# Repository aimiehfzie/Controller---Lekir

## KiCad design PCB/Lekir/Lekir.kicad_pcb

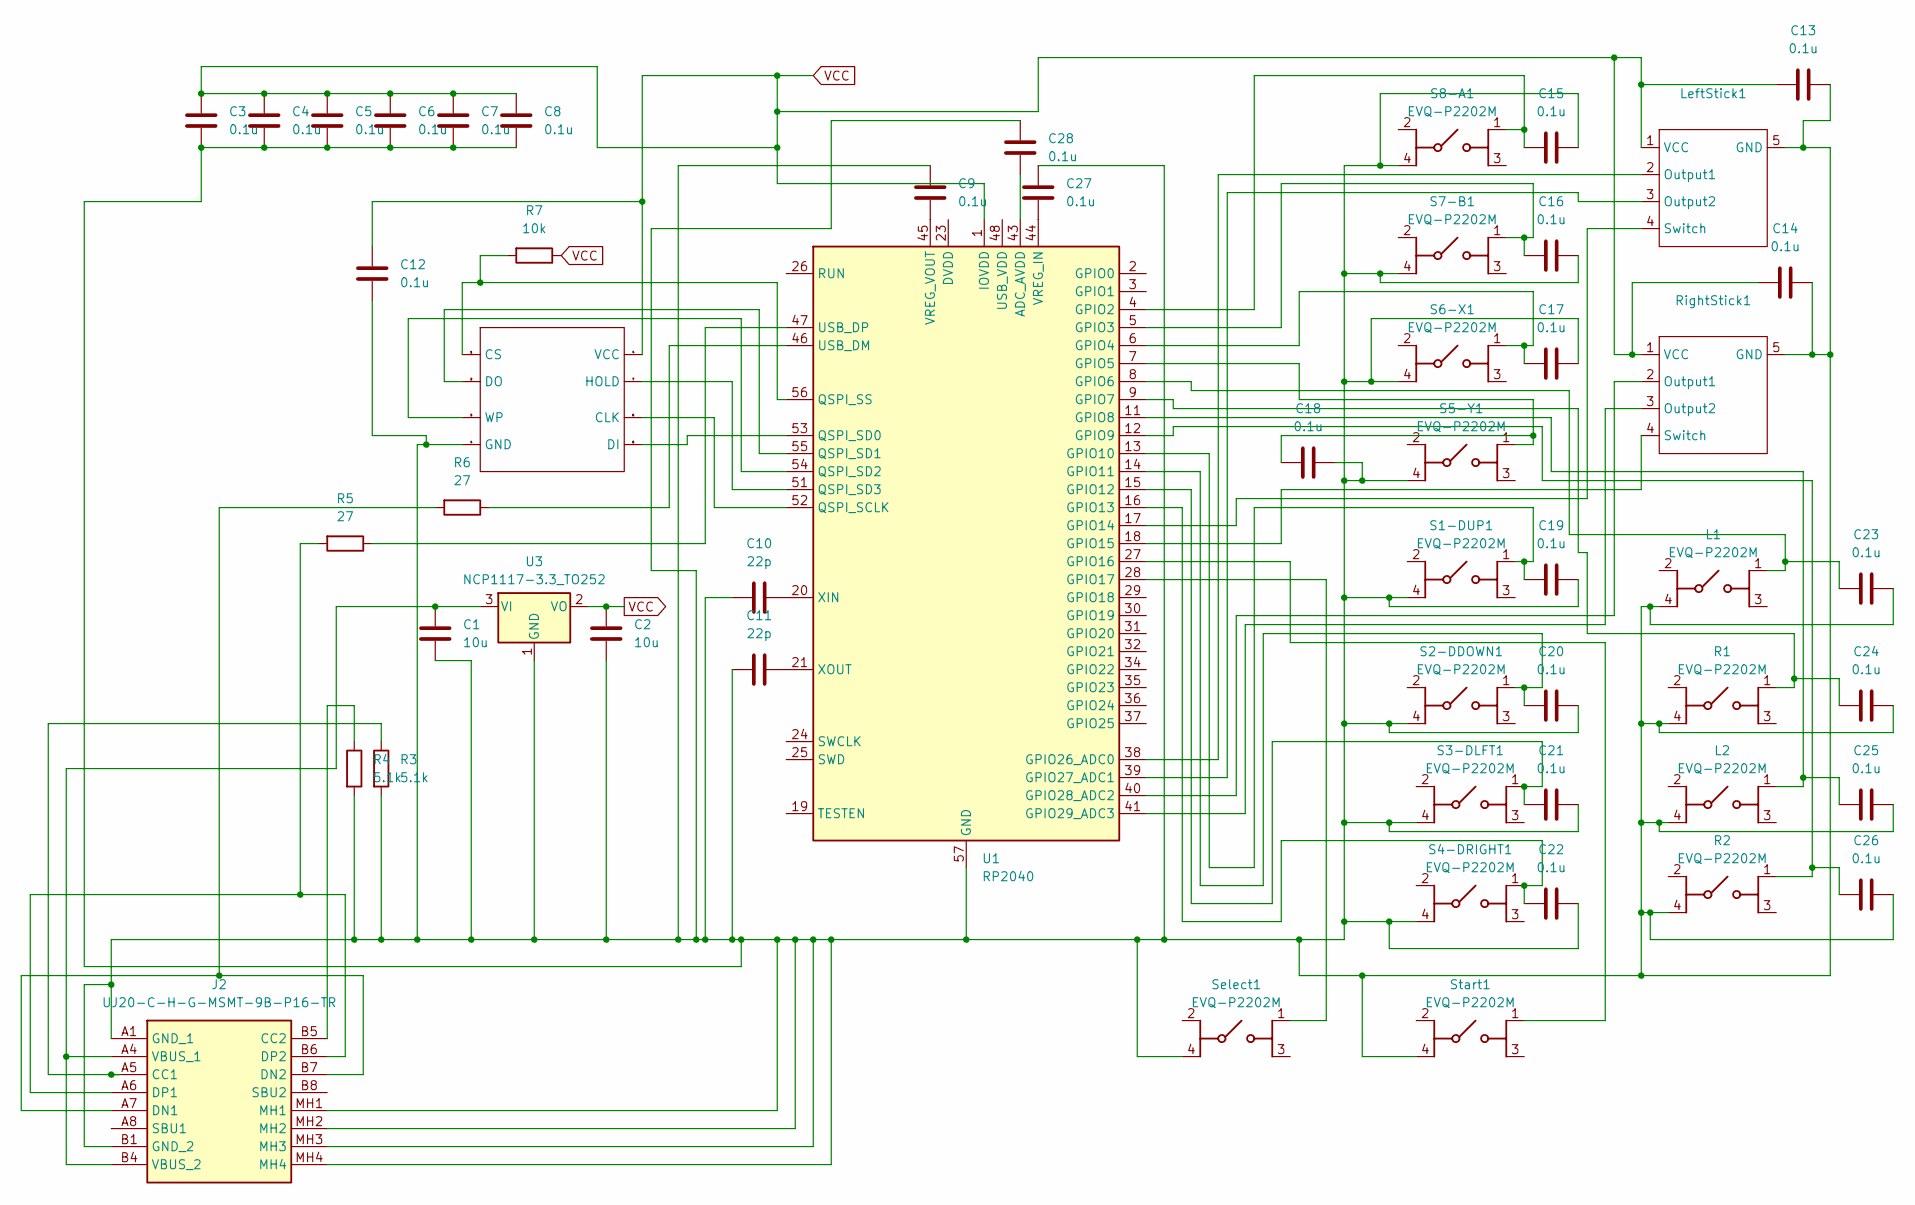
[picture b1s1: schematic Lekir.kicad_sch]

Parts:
C1, C2: 10u; CAPC1005X70N
C3, C4, C5, C6, C7, C8, C9, C12, C13, C14, C15, C16, C17, C18, C19, C20, C21, C22, C23, C24, C25, C26, C27, C28: 0.1u; CAPC1005X55N
C10, C11: 22p; CAPC1608X90N
J2: UJ20-C-H-G-MSMT-9B-P16-TR; UJ20CHGMSMT9BP16TR; Manufacturer_Part_Number UJ20-C-H-G-MSMT-9B-P16-TR
L1, L2: EVQ-P2202M; EVQP2202M; Mouser Part Number 667-EVQ-P2202M
LeftStick1: JH16-KSilver
R1, R2: EVQ-P2202M; EVQP2202M; Mouser Part Number 667-EVQ-P2202M
R3, R4: 5.1k; RESC3216X70N
R5, R6: 27; ERA2AED122X
R7: 10k; ERA2AED122X
RightStick1: JH16-KSilver
S1-DUP1, S2-DDOWN1, S3-DLFT1, S4-DRIGHT1, S5-Y1, S6-X1, S7-B1, S8-A1: EVQ-P2202M; EVQP2202M; Mouser Part Number 667-EVQ-P2202M
Select1: EVQ-P2202M; EVQP2202M; Mouser Part Number 667-EVQ-P2202M
Start1: EVQ-P2202M; EVQP2202M; Mouser Part Number 667-EVQ-P2202M
U1: RP2040; QFN-56-1EP_7x7mm_P0.4mm_EP3.2x3.2mm
U2: Flash
U3: NCP1117-3.3_TO252; TO-252-2

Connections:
unnamed: J2.A5 (CC1), R3.1
unnamed: J2.B5 (CC2), R4.1
unnamed: J2.A7 (DN1), J2.B7 (DN2), R6.2
unnamed: J2.A6 (DP1), J2.B6 (DP2), R5.2
unnamed: C1.1, J2.A4 (VBUS_1), J2.B4 (VBUS_2), U3.3 (VI)
unnamed: C23.2, L1.1 (NO_1), U1.8 (GPIO6)
unnamed: C25.2, L2.1 (NO_1), U1.11 (GPIO8)
unnamed: LeftStick1.2 (Output1), U1.38 (GPIO26_ADC0)
unnamed: LeftStick1.3 (Output2), U1.39 (GPIO27_ADC1)
unnamed: LeftStick1.4 (Switch), U1.17 (GPIO14)
unnamed: C24.2, R1.1 (NO_1), U1.9 (GPIO7)
unnamed: C26.2, R2.1 (NO_1), U1.12 (GPIO9)
unnamed: RightStick1.2 (Output1), U1.40 (GPIO28_ADC2)
unnamed: RightStick1.3 (Output2), U1.41 (GPIO29_ADC3)
unnamed: RightStick1.4 (Switch), U1.18 (GPIO15)
unnamed: C19.2, S1-DUP1.1 (NO_1), U1.13 (GPIO10)
unnamed: C20.2, S2-DDOWN1.1 (NO_1), U1.14 (GPIO11)
unnamed: C21.2, S3-DLFT1.1 (NO_1), U1.15 (GPIO12)
unnamed: C22.2, S4-DRIGHT1.1 (NO_1), U1.16 (GPIO13)
unnamed: C18.2, S5-Y1.1 (NO_1), U1.7 (GPIO5)
unnamed: C17.2, S6-X1.1 (NO_1), U1.6 (GPIO4)
unnamed: C16.2, S7-B1.1 (NO_1), U1.5 (GPIO3)
unnamed: C15.2, S8-A1.1 (NO_1), U1.4 (GPIO2)
unnamed: Select1.1 (NO_1), U1.28 (GPIO17)
unnamed: Start1.1 (NO_1), U1.27 (GPIO16)
unnamed: C28.2, U1.43 (ADC_AVDD)
unnamed: U1.23 (DVDD), U1.50 (DVDD)
unnamed: U1.52 (QSPI_SCLK), U2.6 (CLK)
unnamed: U1.53 (QSPI_SD0), U2.5 (DI)
unnamed: U1.55 (QSPI_SD1), U2.2 (DO)
unnamed: U1.54 (QSPI_SD2), U2.3 (WP)
unnamed: U1.51 (QSPI_SD3), U2.7 (HOLD)
unnamed: R7.2, U1.56 (QSPI_SS), U2.1 (CS)
unnamed: R6.1, U1.46 (USB_DM)
unnamed: R5.1, U1.47 (USB_DP)
unnamed: C27.2, U1.44 (VREG_IN)
unnamed: C9.2, U1.45 (VREG_VOUT)
unnamed: C10.1, U1.20 (XIN)
unnamed: C11.1, U1.21 (XOUT)

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
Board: 2 copper layers, 53 parts (0 on the bottom side), 41 nets, no tracks yet.

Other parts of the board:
S1: EVQ-P2202M; EVQP2202M

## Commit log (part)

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2026-06-23 Schematics for buttons are complete
